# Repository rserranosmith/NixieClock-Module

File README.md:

# NixieClock-Module
Module that abstracts the nixie tube clock to digital signals

## Signals
The following signals are meant to be multiplexed (one signal should be active at a time). You activate the signal by pulling it high.
N1 - First Nixie Tube
N2  - Second Nixie Tube
SEP - Separator
N3  - Third Nixie Tube
N4  - Fourth Nixie Tube

The following Truth Table shows how to interface with the K155NA1 IC.

| D | C | B | A | Res |
| --- | --- | --- | --- | --- |
| L | L | L | L | 0 |
| L | L | L | H | 1 |
| L | L | H | L | 2 |
| L | L | H | H | 3 |
| L | H | L | L | 4 |
| L | H | L | H | 5 |
| L | H | H | L | 6 |
| L | H | H | H | 7 |
| H | L | L | L | 8 |
| H | L | L | H | 9 |

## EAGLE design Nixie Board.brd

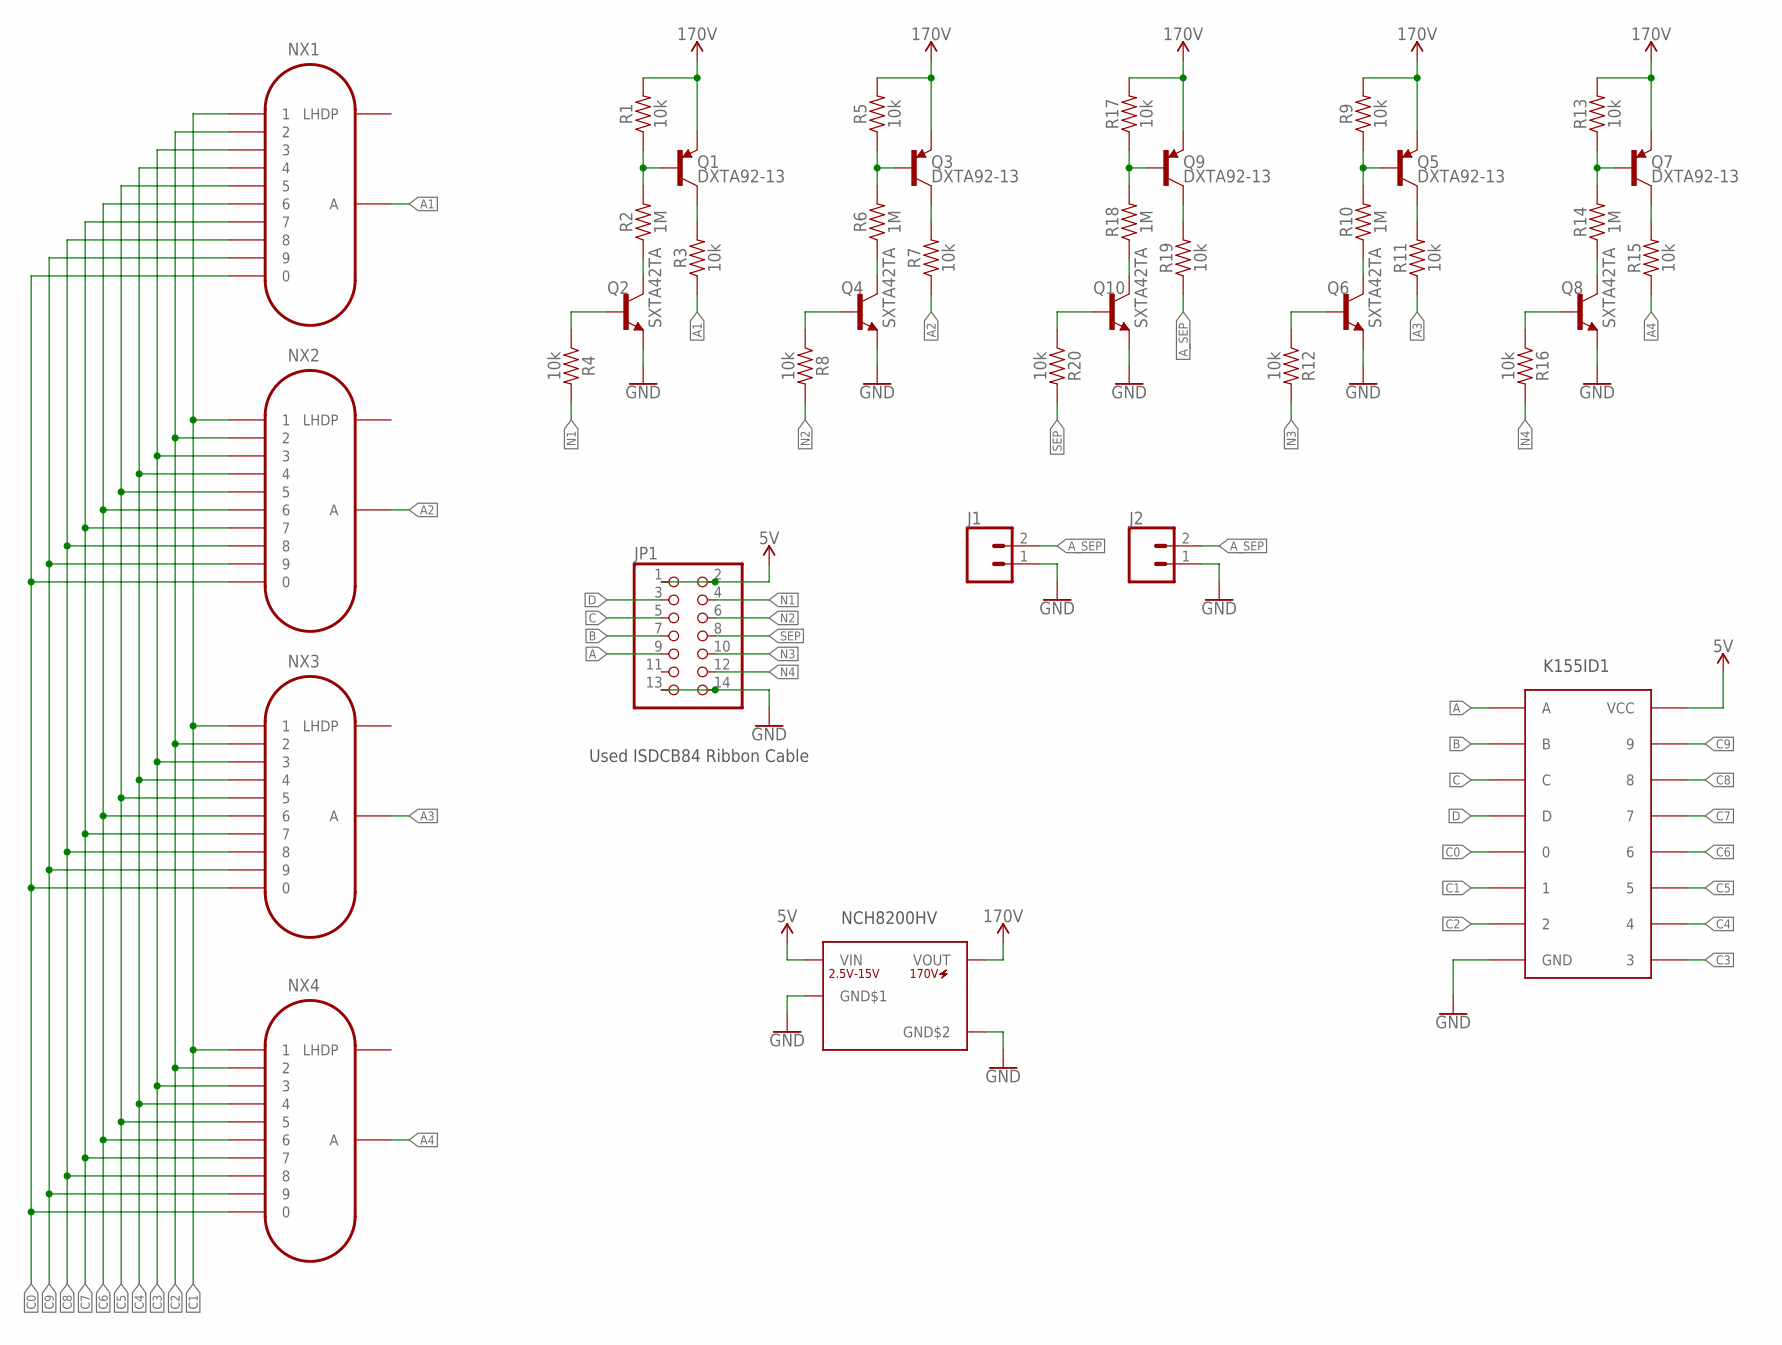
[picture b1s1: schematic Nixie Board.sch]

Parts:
J1, J2: CONN_02; 1X02; MPN INS-1
JP1: PINHD-2X7; 2X07; MPN 30314-6002HB
NX1, NX2, NX3, NX4: IN-12BNOHOLE; IN-12-DSUB-NOHOLE; MPN IN-12B
Q1, Q3, Q5, Q7, Q9: DXTA92-13; DXTA9213; MPN DXTA92-13
Q2, Q4, Q6, Q8, Q10: SXTA42TA; MPN SXTA42TA
R1, R3, R4, R5, R7, R8, R9, R11, R12, R13, R15, R16, R17, R19, R20: 10k; 0603; MPN ESR03EZPJ103
R2, R6, R10, R14, R18: 1M; 0603; MPN ERJ-3EKF1004V
U$1: K155ID1; DIP16; MPN K155ID1
U$2: NCH8200HV; MPN NCH8200HV

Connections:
5V: JP1.1, JP1.2, U$1.5 (VCC), U$2.P$1 (VIN)
A: JP1.9, U$1.3 (A)
A1: NX1.A, R3.1
A2: NX2.A, R7.1
A3: NX3.A, R11.1
A4: NX4.A, R15.1
A_SEP: J1.2, J2.2, R19.1
B: JP1.7, U$1.6 (B)
C: JP1.5, U$1.7 (C)
C0: NX1.0, NX2.0, NX3.0, NX4.0, U$1.16 (0)
C1: NX1.1, NX2.1, NX3.1, NX4.1, U$1.15 (1)
C2: NX1.2, NX2.2, NX3.2, NX4.2, U$1.8 (2)
C3: NX1.3, NX2.3, NX3.3, NX4.3, U$1.9 (3)
C4: NX1.4, NX2.4, NX3.4, NX4.4, U$1.13 (4)
C5: NX1.5, NX2.5, NX3.5, NX4.5, U$1.14 (5)
C6: NX1.6, NX2.6, NX3.6, NX4.6, U$1.11 (6)
C7: NX1.7, NX2.7, NX3.7, NX4.7, U$1.10 (7)
C8: NX1.8, NX2.8, NX3.8, NX4.8, U$1.1 (8)
C9: NX1.9, NX2.9, NX3.9, NX4.9, U$1.2 (9)
D: JP1.3, U$1.4 (D)
GND: J1.1, J2.1, JP1.13, JP1.14, Q2.3 (E), Q4.3 (E), Q6.3 (E), Q8.3 (E), Q10.3 (E), U$1.12 (GND), U$2.P$2 (GND$1), U$2.P$3 (GND$2)
N1: JP1.4, R4.2
N2: JP1.6, R8.2
N3: JP1.10, R12.2
N4: JP1.12, R16.2
unnamed: Q1.1 (B), R1.1, R2.2
unnamed: Q1.2 (C), R3.2
unnamed: Q2.2 (C), R2.1
unnamed: Q2.1 (B), R4.1
unnamed: Q3.1 (B), R5.1, R6.2
unnamed: Q3.2 (C), R7.2
unnamed: Q4.2 (C), R6.1
unnamed: Q4.1 (B), R8.1
unnamed: Q5.1 (B), R9.1, R10.2
unnamed: Q5.2 (C), R11.2
unnamed: Q6.2 (C), R10.1
unnamed: Q6.1 (B), R12.1
unnamed: Q7.1 (B), R13.1, R14.2
unnamed: Q7.2 (C), R15.2
unnamed: Q8.2 (C), R14.1
unnamed: Q8.1 (B), R16.1
unnamed: Q9.1 (B), R17.1, R18.2
unnamed: Q9.2 (C), R19.2
unnamed: Q10.2 (C), R18.1
unnamed: Q10.1 (B), R20.1
SEP: JP1.8, R20.2
VCC_1: Q1.3 (E), Q3.3 (E), Q5.3 (E), Q7.3 (E), Q9.3 (E), R1.2, R5.2, R9.2, R13.2, R17.2, U$2.P$4 (VOUT)

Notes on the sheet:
K155ID1
NCH8200HV
Used ISDCB84 Ribbon Cable

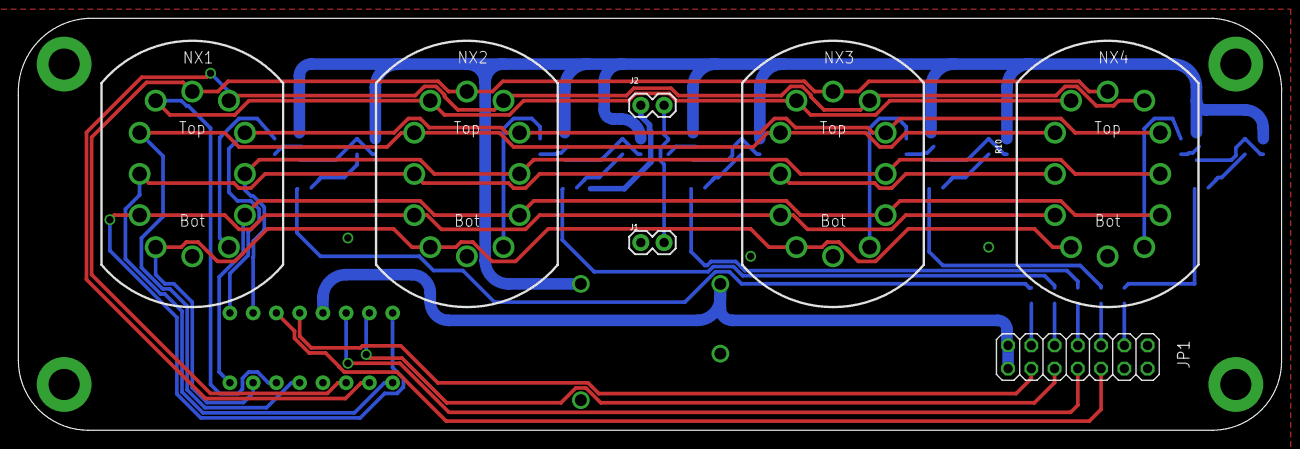
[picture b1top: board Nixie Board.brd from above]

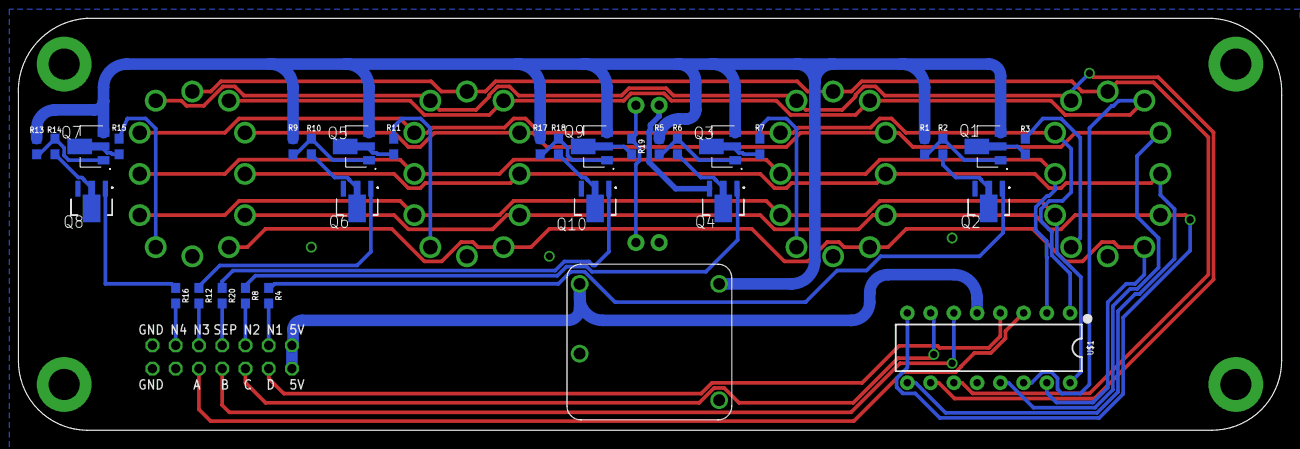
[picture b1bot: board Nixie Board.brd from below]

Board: 2 copper layers, 138.0 x 45.0 mm, 39 parts (32 on the bottom side), 47 nets.

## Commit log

2022-11-17 feat: first version of Nixie Clock - Ordered via JLCPCB
2022-11-17 chore: created PDF of circuit schematic
2022-11-17 chore: added bom and MPN to components
2022-12-21 Added signals

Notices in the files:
parts and their libraries:
SparkFun-Connectors: Licensing: Creative Commons ShareAlike 4.0 International - https://creativecommons.org/licenses/by-sa/4.0
